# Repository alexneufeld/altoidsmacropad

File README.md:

# 12 Key Altoids Tin MacroPad

By Alex Neufeld, 2021

### Features:
- 12 cherry style mechanical keyswitches
- Custom PCB
- QMK firmware via a Sparkfun Pro Micro clone

### Building

The design files as available in this repo. I don't have a formal build guide, sorry. 

If you just want to get some PCBs made, there is a gerber .zip file in the `pcb` directory.

I cut the top of the case with a cutoff wheel in a rotary tool. There is a printable template in the `case` directory that I attached with spray adhesive and cut through.

Quick note on the firmware side of things: QMK is very new to me. the `firmware` directory has a proof of concept fileset that was enough to get a basic keymap onto my board. You're on your own if you want to add fancier features (layers, etc.) 

### BOM

| Part      | Quantity | Example source                                           |
|-----------|----------|----------------------------------------------------------|
| Case      | 1        | [LINK](https://www.amazon.com/dp/B07GG67NNH/)            |
| Switches  | 12       | [LINK](https://www.aliexpress.com/item/32862816873.html) |
| Keycaps   | 12       | [LINK](https://www.aliexpress.com/item/32830177884.html) |
| Pro Micro | 1        | [LINK](https://www.aliexpress.com/item/32768308647.html) |
| Diodes    | 12       | [LINK](https://www.digikey.ca/short/m5v7m70m)            |

### Gallery

CAD design

3D printed plate, the mint tin sheet metal is too thin to securely hold the switches.

PCB ready to go.

Testing with the Pro-Micro clone.

Upper assembly soldered and ready.

Add felt pads to the bottom of the case.

Steel plate for inertia, kapton tape to insulate the electronics from contact with metal parts.

Finished! rear view with cutout for USB-in.

Kailh box jade switches and clear, blank PBT keycaps installed.

### Schematic

## Acknowledgments

This project was inspired in part by the [2% milk keyboard.](https://github.com/Spaceman/SpaceboardsHardware/tree/master/Keyboards/2%25%20Milk)

Ruiqi Mao's [Keyboard PCB guide](https://github.com/ruiqimao/keyboard-pcb-guide#production) was very helpful.

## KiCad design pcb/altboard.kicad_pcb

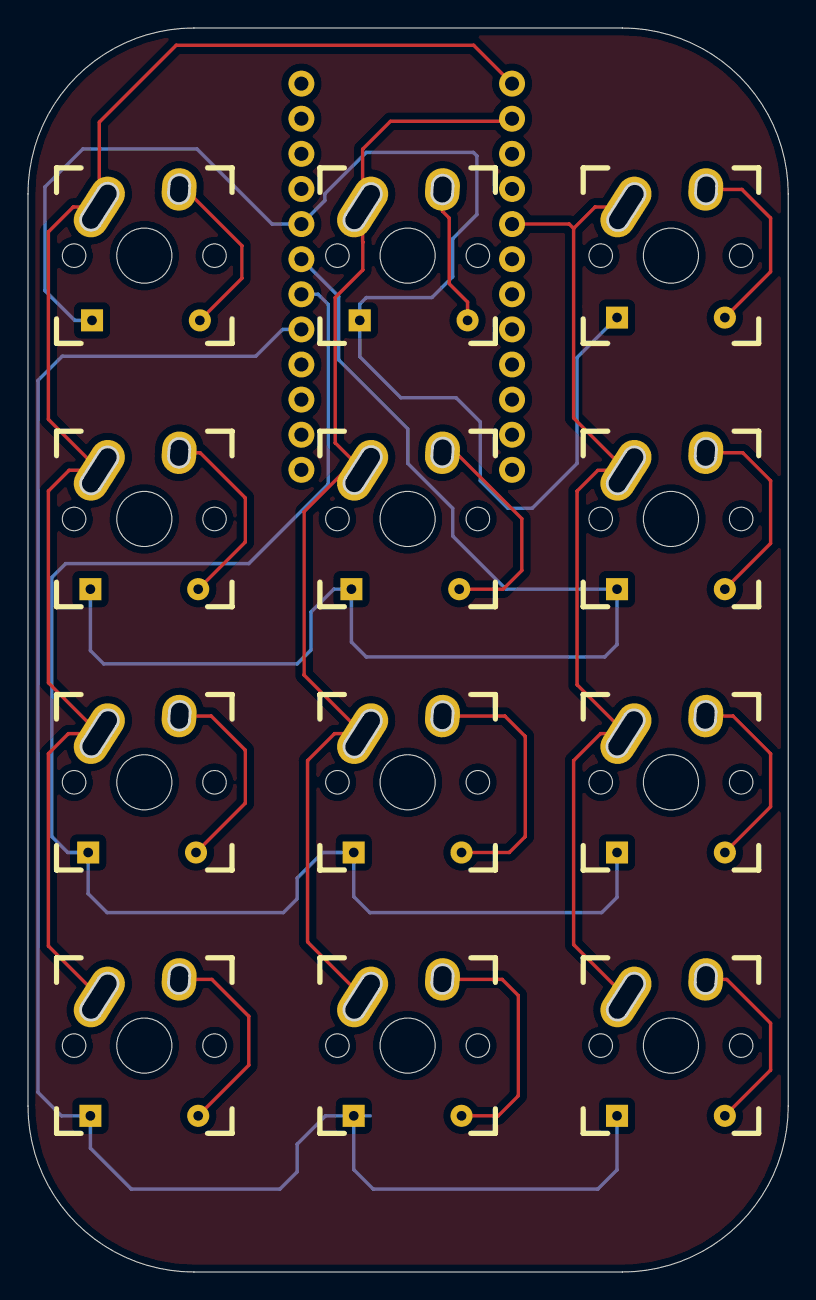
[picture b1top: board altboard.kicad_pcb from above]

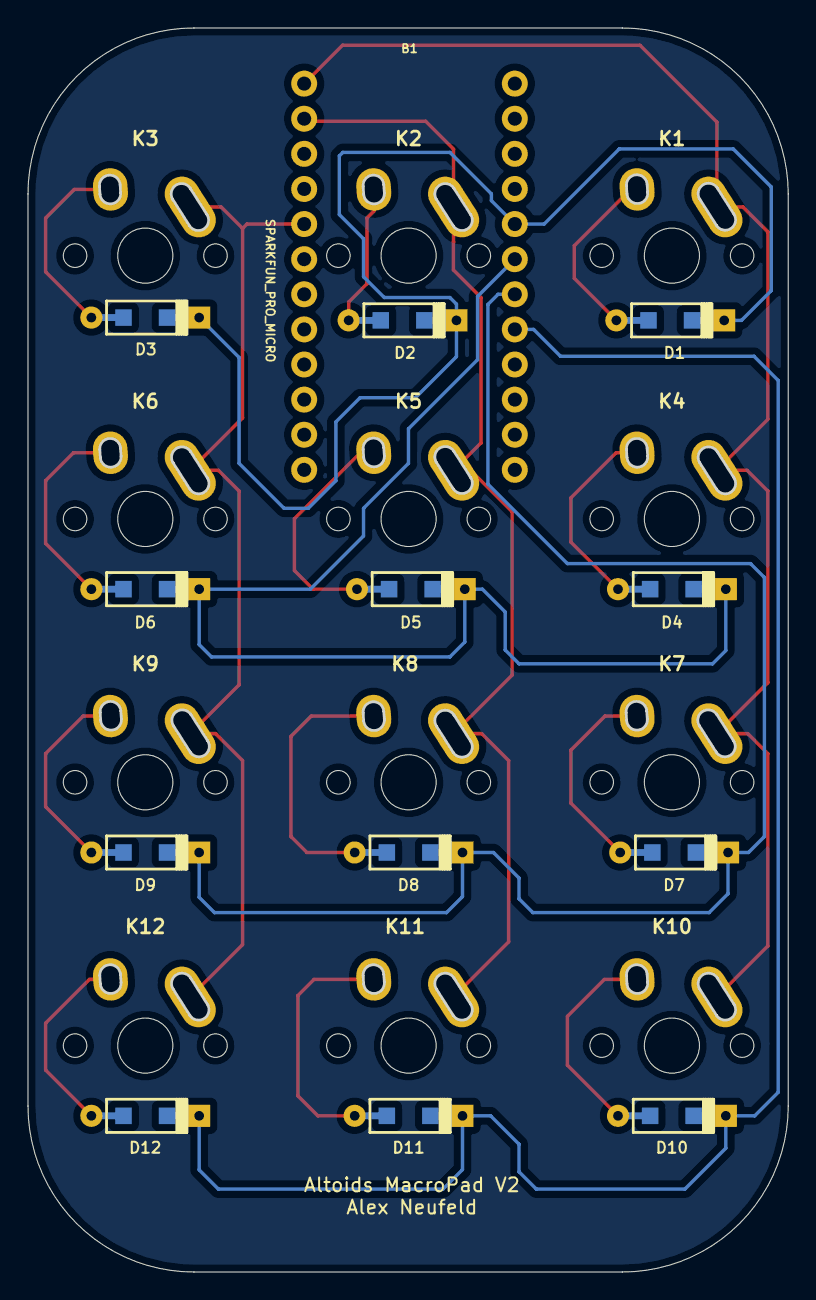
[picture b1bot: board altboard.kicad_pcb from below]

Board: 2 copper layers, 55.0 x 90.0 mm, 25 parts (13 on the bottom side), 19 nets.

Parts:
B1: SPARKFUN_PRO_MICRO
D1, D2, D3, D4, D5, D6, D7, D8, D9, D10, D11, D12: D; D_SOD123_axial
K1, K2, K3, K4, K5, K6, K7, K8, K9, K10, K11, K12: KEYSW; Mx_Alps_100

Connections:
unnamed: B1.1, K1.1, K4.1, K7.1, K10.1
unnamed: B1.2, K2.1, K5.1, K8.1, K11.1
unnamed: B1.5, K3.1, K6.1, K9.1, K12.1
unnamed: B1.17, D10.1, D11.1, D12.1
unnamed: B1.18, D7.1, D8.1, D9.1
unnamed: B1.19, D4.1, D5.1, D6.1
unnamed: B1.20, D1.1, D2.1, D3.1
unnamed: D1.2, K1.2
unnamed: D2.2, K2.2
unnamed: D3.2, K3.2
unnamed: D4.2, K4.2
unnamed: D5.2, K5.2
unnamed: D6.2, K6.2
unnamed: D7.2, K7.2
unnamed: D8.2, K8.2
unnamed: D9.2, K9.2
unnamed: D10.2, K10.2
unnamed: D11.2, K11.2
unnamed: D12.2, K12.2

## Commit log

2021-05-06 init
